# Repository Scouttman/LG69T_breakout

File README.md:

# LG69T_breakout
RTK LG69T break out board

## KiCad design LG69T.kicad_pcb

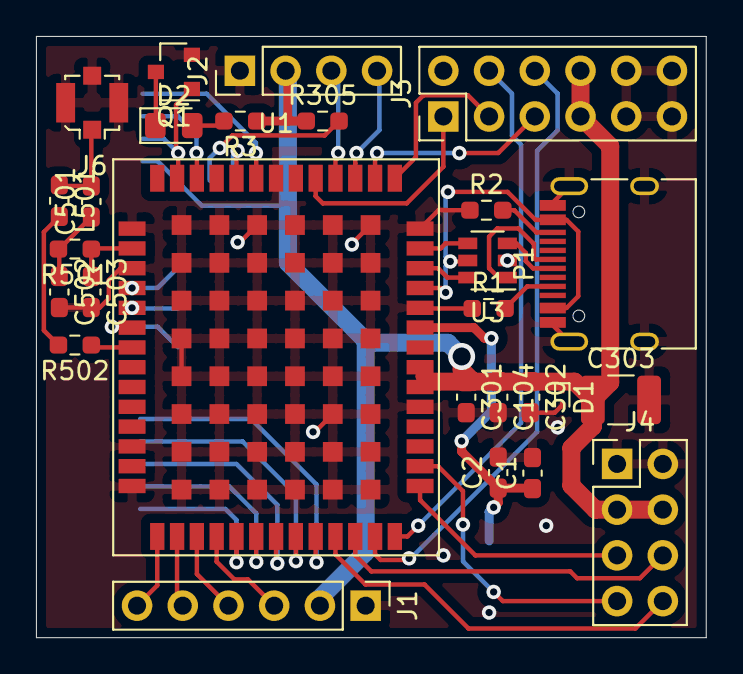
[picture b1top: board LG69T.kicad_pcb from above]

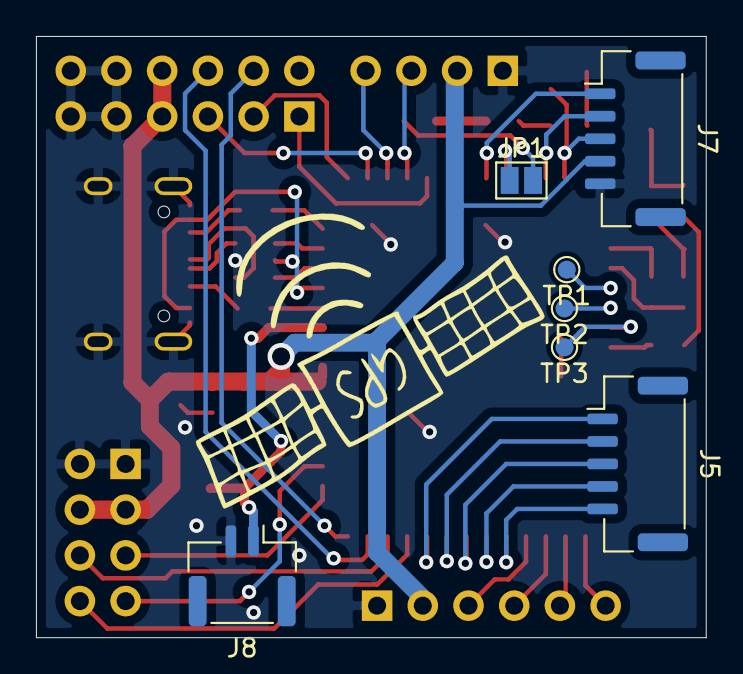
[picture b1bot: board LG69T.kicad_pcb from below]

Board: 2 copper layers, 37.2 x 33.4 mm, 34 parts (7 on the bottom side), 44 nets.

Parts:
C1: 4.7uF; C_0603_1608Metric_Pad1.08x0.95mm_HandSolder
C2, C104, C302: 100nF; C_0603_1608Metric_Pad1.08x0.95mm_HandSolder
C301: 1nF; C_0603_1608Metric_Pad1.08x0.95mm_HandSolder
C303: 100uF; C_1210_3225Metric_Pad1.33x2.70mm_HandSolder
C501: 100pF; C_0603_1608Metric_Pad1.08x0.95mm_HandSolder
C502, C503: DNP; C_0603_1608Metric_Pad1.08x0.95mm_HandSolder
D1: DIAC; D_SOD-923
D2: LED; LED_0805_2012Metric_Pad1.15x1.40mm_HandSolder
J1: Conn_01x06; PinHeader_1x06_P2.54mm_Vertical
J2: Conn_01x04; PinHeader_1x04_P2.54mm_Vertical
J3: Conn_02x06_Odd_Even; PinHeader_2x06_P2.54mm_Vertical
J4: Conn_02x04_Odd_Even; PinHeader_2x04_P2.54mm_Vertical
J5, J7: Conn_01x05_Male; JST_GH_BM05B-GHS-TBT_1x05-1MP_P1.25mm_Vertical
J6: Conn_Coaxial; U.FL_Molex_MCRF_73412-0110_Vertical
J8: Conn_01x02; JST_GH_BM02B-GHS-TBT_1x02-1MP_P1.25mm_Vertical
JP1: Jumper; SolderJumper-2_P1.3mm_Open_Pad1.0x1.5mm
L501: 68nH; L_0603_1608Metric_Pad1.05x0.95mm_HandSolder
P1: USB_C_Plug_USB2.0; USB_C_Receptacle_HRO_TYPE-C-31-M-12
Q1: DTC143Z; SOT-23
R1, R2: 5.1k; R_0603_1608Metric_Pad0.98x0.95mm_HandSolder
R3, R305: 1k; R_0603_1608Metric_Pad0.98x0.95mm_HandSolder
R501: 0R; R_0603_1608Metric_Pad0.98x0.95mm_HandSolder
R502: 10R; R_0603_1608Metric_Pad0.98x0.95mm_HandSolder
TP1, TP2, TP3: TestPoint; TestPoint_Pad_D1.0mm
U1: LG69T
U3: USBLC6-2SC6; SOT-23-6

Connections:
/CAN1_RX: J4.8, U1.24
/CAN1_TX: J4.6, U1.25
/CAN2_RX: J4.7, U1.29
/CAN2_TX: J4.5, U1.28
/FWD: J5.2, U1.22
/GeoFence: J5.5, U1.19
/I2C_SCL: J2.3, U1.45
/I2C_SDA: J2.4, U1.44
/PPS: J7.3, Q1.1, U1.53
/RF_in: C503.1, R501.1, U1.2
/RTK_ind: J5.4, U1.20
/Reset_N: J7.1, U1.49
/SPI_CLK: J1.6, U1.15
/SPI_CS: J1.3, U1.18
/SPI_MISO: J1.4, U1.17
/SPI_MOSI: J1.5, U1.16
/UART1_RX: J3.5, U1.43
/UART1_Ready: J3.1, U1.46
/UART1_TX: J3.3, U1.42
/UART2_RX: J3.6, U1.26
/UART2_TX: J3.4, U1.27
/USB_DM: P1.A7, U1.39, U3.1, U3.6
/USB_DP: P1.A6, U1.40, U3.3, U3.4
/USB_VBUS: P1.A4, P1.A9, P1.B4, P1.B9, U1.38, U3.5
/VCC_RF: R502.1, U1.7
/V_Backup: C1.1, C2.1, J8.1, U1.36
/WI: J5.1, U1.23
/Wake_up: J7.2, U1.52
/Wheel_Tick: J5.3, U1.21
GND: C1.2, C2.2, C104.2, C301.2, C302.2, C303.2, C502.2, C503.2, D1.2, J1.1, J2.1, J3.9, J3.10, J3.11, J3.12, J4.1, J4.2, J6.2, J7.5, J8.2, P1.A1, P1.A12, P1.B1, P1.B12, P1.S1, Q1.2, R1.1, R2.1, U1.1, U1.3, U1.12, U1.14, U1.32, U1.37, U1.41, U1.48, U1.55, U3.2
unnamed: C501.1, C502.1, R501.2
unnamed: C501.2, J6.1, L501.1
unnamed: D2.1, Q1.3
unnamed: D2.2, R3.2
unnamed: JP1.1, U1.50
unnamed: JP1.2, R305.2
unnamed: L501.2, R502.2
unnamed: P1.A5, R1.2
unnamed: P1.B5, R2.2
unnamed: TP1.1, U1.4
unnamed: TP2.1, U1.5
unnamed: TP3.1, U1.6
unnamed: U1.8, U1.9, U1.10, U1.11, U1.13, U1.30, U1.31, U1.35, U1.47, U1.51, U1.54
VCC: C104.1, C301.1, C302.1, C303.1, D1.1, J1.2, J2.2, J3.7, J3.8, J4.3, J4.4, J7.4, R3.1, R305.1, U1.33, U1.34

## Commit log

2022-07-16 added files
2022-07-16 add photo
